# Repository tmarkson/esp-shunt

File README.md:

View this project on [CADLAB.io](https://cadlab.io/project/25133). 

# esp-shunt
A wifi power sensor based on ESP-01 and shunt resistor. Works well with ESPHome.

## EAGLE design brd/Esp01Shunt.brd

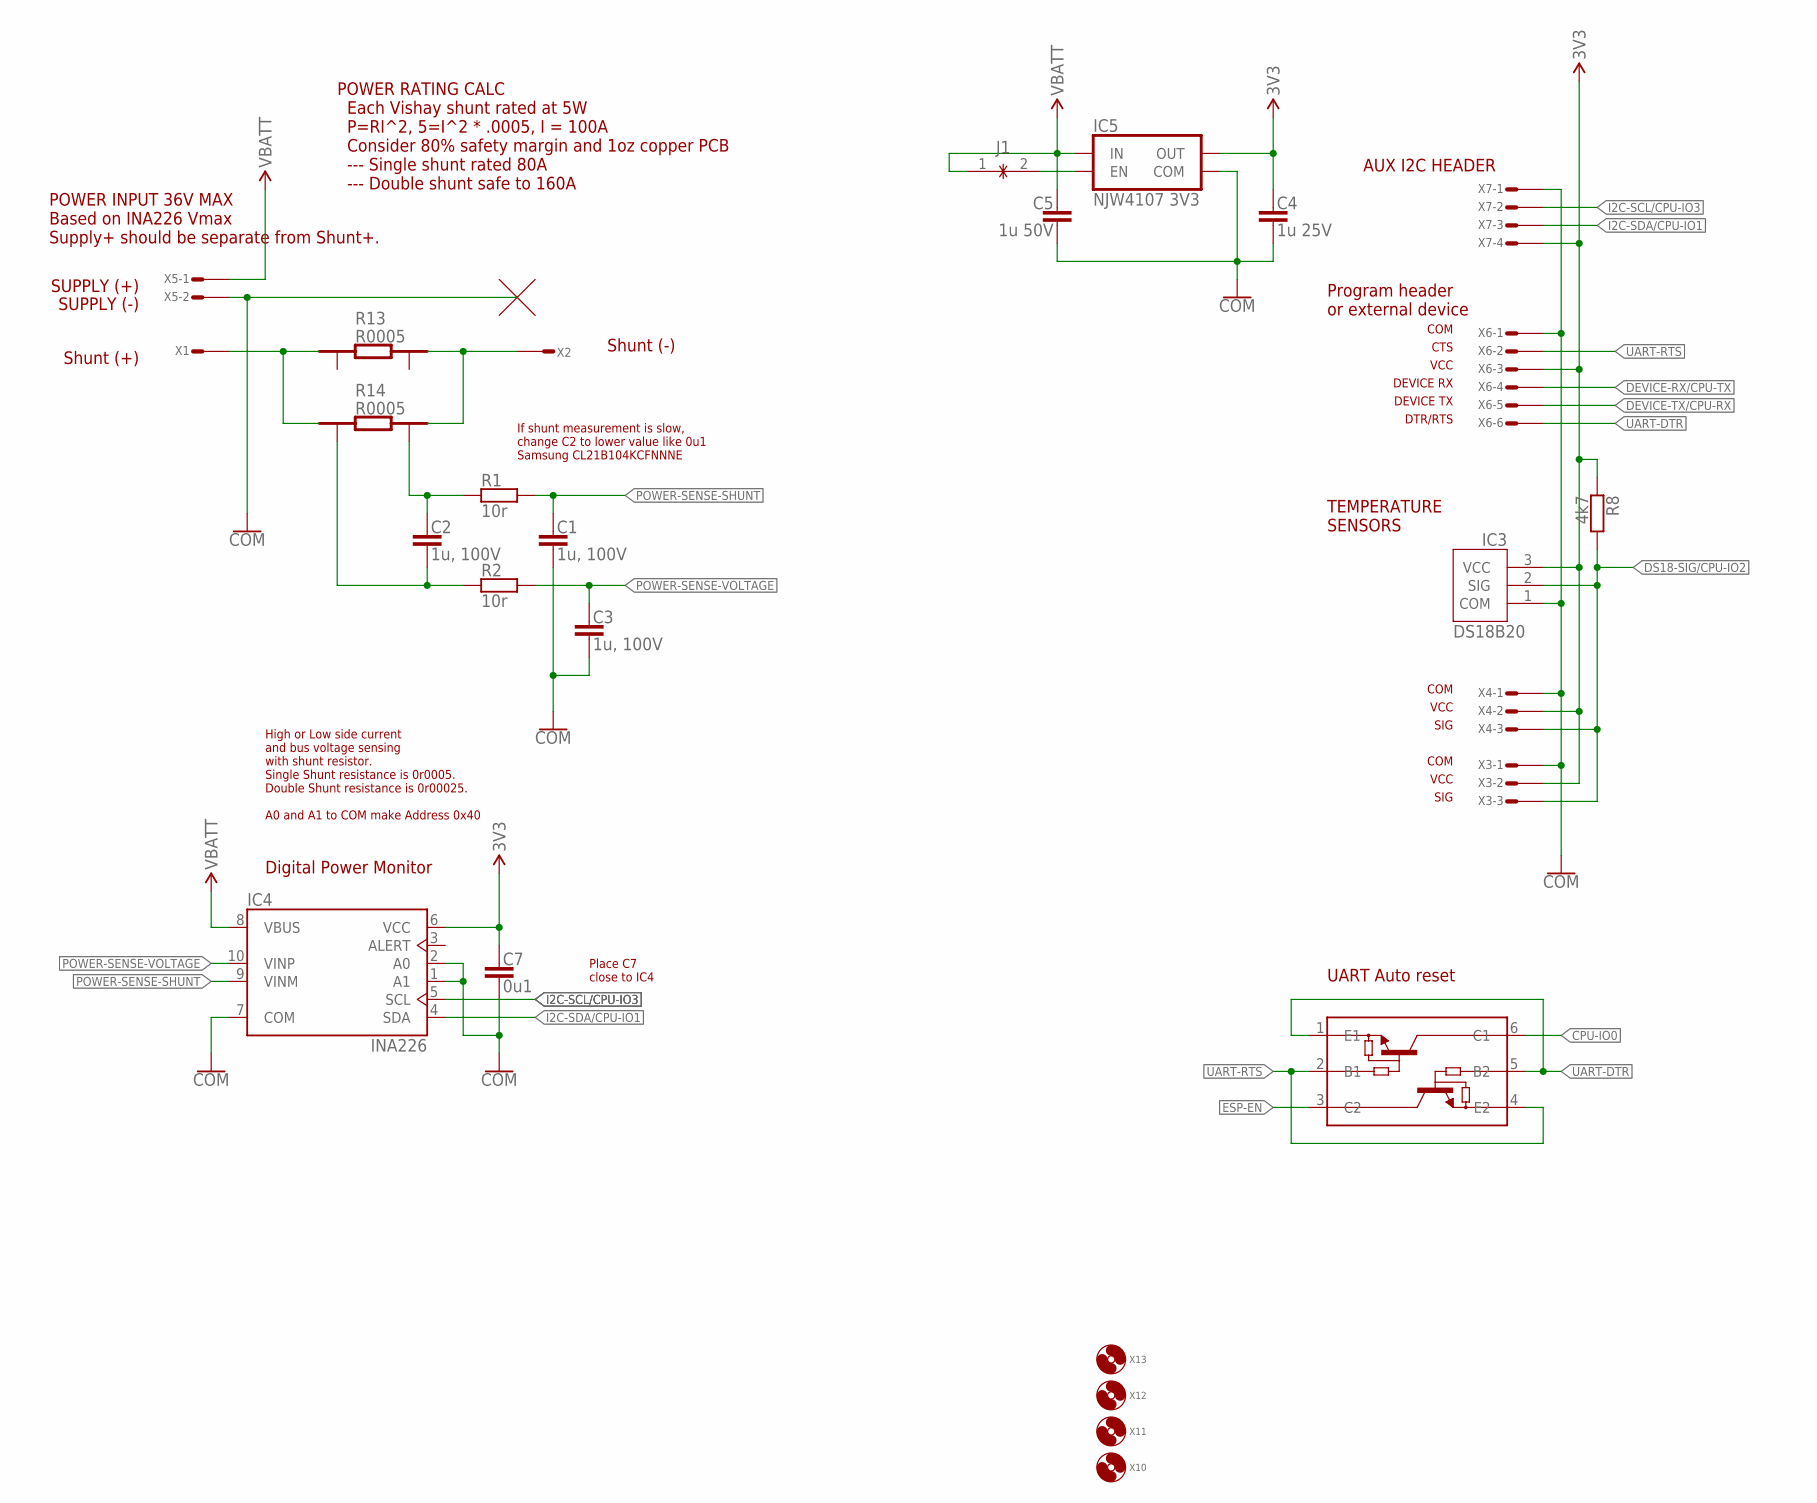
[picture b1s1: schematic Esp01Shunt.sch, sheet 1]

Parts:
C1, C2, C3: 1u, 100V; 1206; MFG_PN CL31B105KCHNNNE
C4: 1u 25V; C0603; MFG_PN C1608X7R1E105K080AE
C5: 1u 50V; C0603; MFG_PN C1608X5R1H105K080AB
C7: 0u1; C0603; MFG_PN VJ0603Y104JXXAC
IC2: MUN5214DW1T1G; TSSOP6; MFG_PN MUN5214DW1T1G
IC3: DS18B20; TO92-INLINE
IC4: INA226; VSSOP10
IC5: NJW4107 3V3; SOT89-5
J1: JUMPER-60X20-NC; JUMPER-60X20
R1, R2: 10r; R0805
R8: 4k7; R0603; MFG_PN ERJ-3GEYJ472V
R13, R14: R0005; RES-SHUNT-WSK1216
X1, X2: CON-SCREW-V-30AMP
X3, X4: CON-1X3
X5: CON-1X2-TERM-SPRING-5MM-2834082-1
X6: CON-1X6-UART-DCE
X7: CON-1X4
X10, X11, X12, X13: HOLE-NO-PAD-NO-SILK; M3-NO-PAD-NO-SILK

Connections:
3V3: C4.1, C7.1, IC3.3 (VCC), IC4.6 (VCC), IC5.4 (OUT), R8.1, X3.2, X4.2, X6.3, X7.4; also elsewhere on the board
COM: C1.2, C3.2, C4.2, C5.2, C7.2, IC3.1 (COM), IC4.1 (A1), IC4.2 (A0), IC4.7 (COM), IC5.2 (COM), IC5.5 (COM), X3.1, X4.1, X5.3, X5.4, X6.1, X7.1; also elsewhere on the board
CPU-IO0: IC2.6 (C1); also elsewhere on the board
DEVICE-RX/CPU-TX: X6.4; also elsewhere on the board
DEVICE-TX/CPU-RX: X6.5; also elsewhere on the board
DS18-SIG/CPU-IO2: IC3.2 (SIG), R8.2, X3.3, X4.3; also elsewhere on the board
ESP-EN: IC2.3 (C2); also elsewhere on the board
I2C-SCL/CPU-IO3: IC4.5 (SCL), X7.2; also elsewhere on the board
I2C-SDA/CPU-IO1: IC4.4 (SDA), X7.3; also elsewhere on the board
unnamed: R13.1, R14.1, X1.1, X1.2, X1.3, X1.4, X1.5, X1.6
unnamed: C2.1, R1.+ (1), R14.3
unnamed: R13.4, R14.4, X2.1, X2.2, X2.3, X2.4, X2.5, X2.6
unnamed: IC5.1 (EN), J1.2
unnamed: C2.2, R2.+ (1), R14.2
POWER-SENSE-SHUNT: C1.1, IC4.9 (VINM), R1.- (2)
POWER-SENSE-VOLTAGE: C3.1, IC4.10 (VINP), R2.- (2)
UART-DTR: IC2.1 (E1), IC2.5 (B2), X6.6
UART-RTS: IC2.2 (B1), IC2.4 (E2), X6.2
VBATT: C5.1, IC4.8 (VBUS), IC5.6 (IN), J1.1, X5.1, X5.2

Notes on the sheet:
Program header or external device
POWER INPUT 36V MAX Based on INA226 Vmax Supply+ should be separate from Shunt+.
Digital Power Monitor
VCC
COM
DEVICE RX
DEVICE TX
High or Low side current and bus voltage sensing with shunt resistor. Single Shunt resistance is 0r0005. Double Shunt resistance is 0r00025. A0 and A1 to COM make Address 0x40
POWER RATING CALC Each Vishay shunt rated at 5W P=RI^2, 5=I^2 * .0005, I = 100A Consider 80% safety margin and 1oz copper PCB --- Single shunt rated 80A --- Double shunt safe to 160A
Shunt (-)
SUPPLY (-)
Shunt (+)
Place C7 close to IC4
If shunt measurement is slow, change C2 to lower value like 0u1 Samsung CL21B104KCFNNNE
TEMPERATURE SENSORS
AUX I2C HEADER
CTS
DTR/RTS
SIG
SUPPLY (+)
UART Auto reset

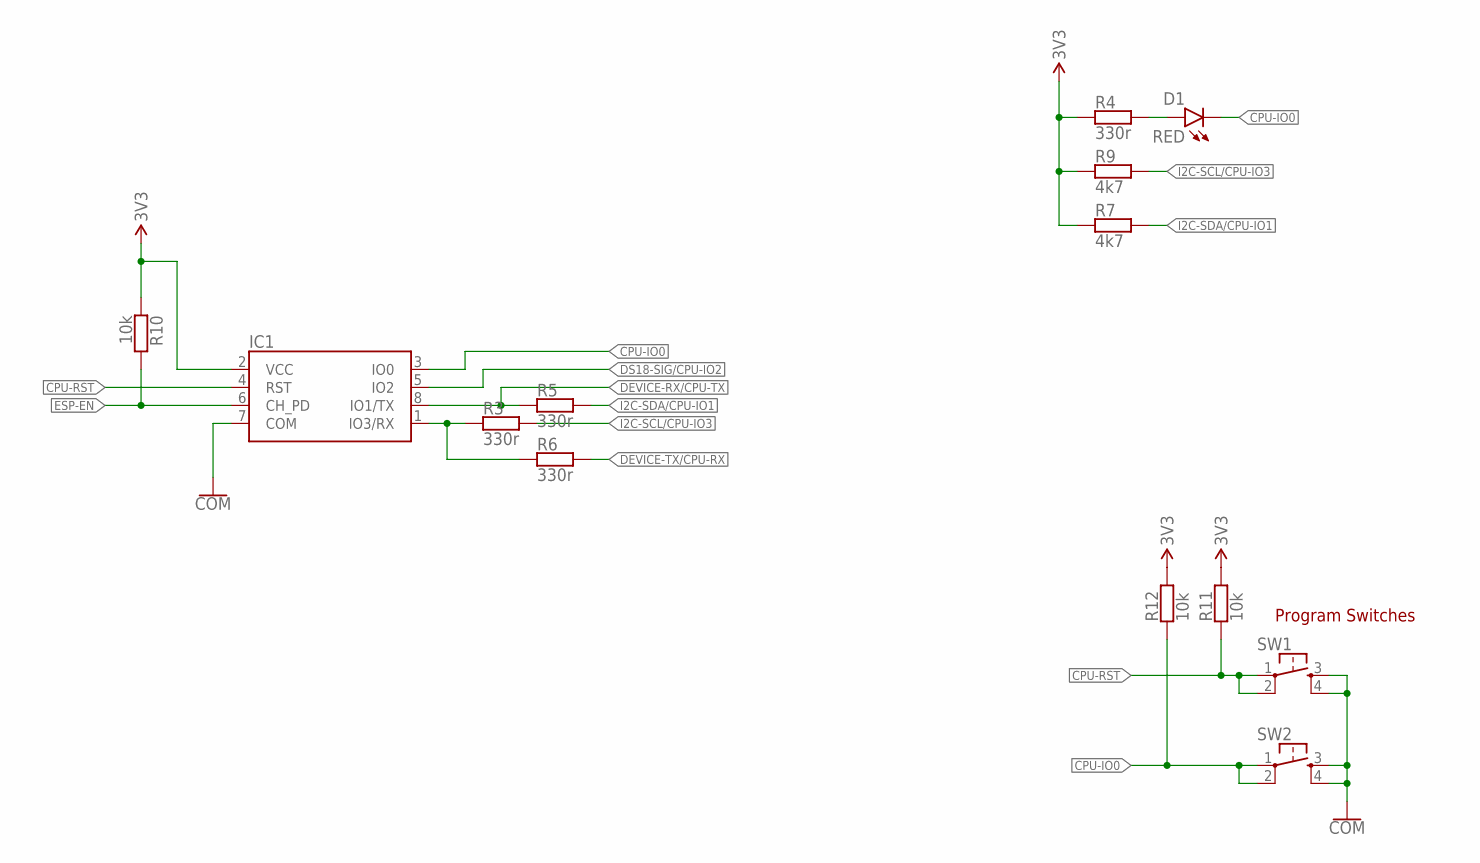
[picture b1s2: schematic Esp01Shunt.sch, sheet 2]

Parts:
D1: RED; LED-0805
IC1: ESP8266-01
R3, R4, R5, R6: 330r; R0603; MFG_PN ERJ-3EKF3300V
R7, R9: 4k7; R0603; MFG_PN ERJ-3GEYJ472V
R10, R11, R12: 10k; R0603; MFG_PN ERJ-3GEYJ103V
SW1, SW2: SWITCH-TACTILE-DOUBLE-SMD; SWITCH-TACTILE-6MM-SMD

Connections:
3V3: IC1.2 (VCC), R4.1, R7.1, R9.1, R10.1, R11.2, R12.2; also elsewhere on the board
COM: IC1.7 (COM), SW1.3, SW1.4, SW2.3, SW2.4; also elsewhere on the board
CPU-IO0: D1.- (C), IC1.3 (IO0), R12.1, SW2.1, SW2.2; also elsewhere on the board
CPU-RST: IC1.4 (RST), R11.1, SW1.1, SW1.2
DEVICE-RX/CPU-TX: IC1.8 (IO1/TX), R5.1; also elsewhere on the board
DEVICE-TX/CPU-RX: R6.2; also elsewhere on the board
DS18-SIG/CPU-IO2: IC1.5 (IO2); also elsewhere on the board
ESP-EN: IC1.6 (CH_PD), R10.2; also elsewhere on the board
I2C-SCL/CPU-IO3: R3.2, R9.2; also elsewhere on the board
I2C-SDA/CPU-IO1: R5.2, R7.2; also elsewhere on the board
unnamed: IC1.1 (IO3/RX), R3.1, R6.1
unnamed: D1.+ (A), R4.2

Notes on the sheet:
Program Switches

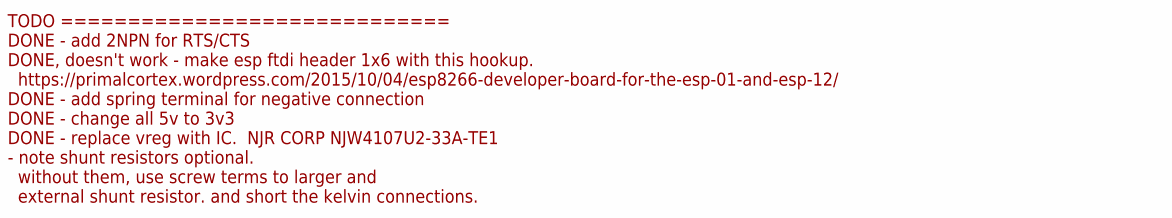
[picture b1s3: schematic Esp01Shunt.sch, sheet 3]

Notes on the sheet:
TODO ============================= DONE - add 2NPN for RTS/CTS DONE, doesn't work - make esp ftdi header 1x6 with this hookup. https://primalcortex.wordpress.com/2015/10/04/esp8266-developer-board-for-the-esp-01-and-esp-12/ DONE - add spring terminal for negative connection DONE - change all 5v to 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

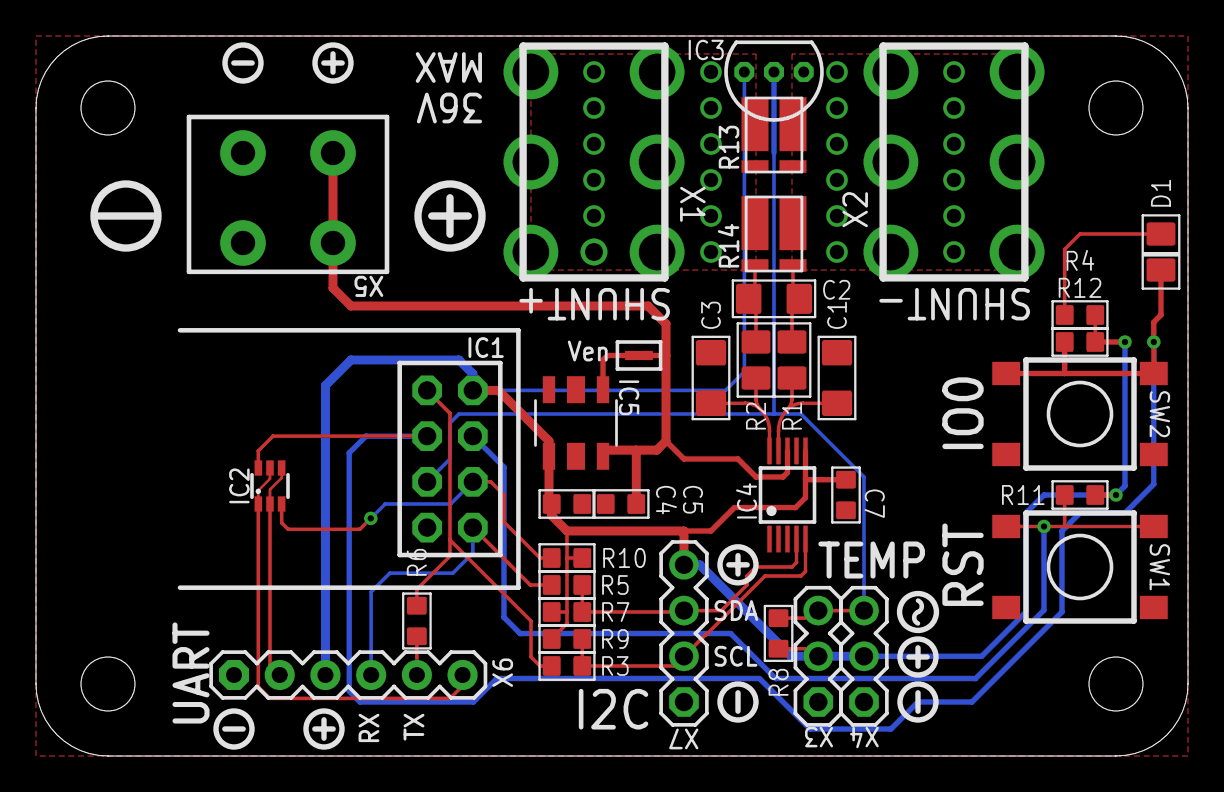
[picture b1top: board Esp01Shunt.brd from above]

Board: 2 copper layers, 64.0 x 40.0 mm, 51 parts (0 on the bottom side), 22 nets.

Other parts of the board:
U$1: SYMBOL-PLUS-SILK
U$2: SYMBOL-MINUS-SILK
U$3, U$4, U$10, U$12: SYMBOL-MINUS-SILK-1MM
U$5, U$9, U$11, U$17: SYMBOL-PLUS-SILK-1MM
U$8: SYMBOL-TILDE-SILK-1MM

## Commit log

2022-01-20 initial
2022-01-20 Backlink to CADLAB.io has been added.
